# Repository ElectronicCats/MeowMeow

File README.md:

# Meow Meow
<p align="center">

<p align=center>

</p>

  Meow Meow es una tarjeta electrónica diseñada por Electronic Cats que simula algunas teclas configurables del teclado y mouse. Meow Meow tiene la característica de poder conectar cualquier material que conduzca la electricidad convirtiendo estos objetos en paneles táctiles. 
  
  Es un kit de experimentos para principiantes y expertos que buscan interactuar entre el mundo real y la tecnología. Meow Meow puede cubrir las áreas de artes plásticas, artes visuales, música, deporte, ingeniería e incluso rehabilitación física.

## ¿A quién va dirigido Meow Meow? 

Para personas de todas las edades, desde niños de 6 años hasta adultos, educadores, artistas, ingenieros, diseñadores, inventores y creadores.

## ¿Cómo funciona? 

  Meow Meow utiliza conmutación de alta capacitancia para detectar cuándo ha realizado una conexión incluso con materiales que no son muy conductores (como hojas, pasta o personas). Meow Meow también puede actuar como un teclado o un mouse. Hay diez  entradas en la placa, a las que puedes conectar los cables caimán y hacer tus propios objetos táctiles.

   La computadora ve a Meow Meow como un teclado (o mouse) común y corriente. Por lo tanto, funciona con todos los programas, sistemas operativos y páginas web, ya que todos los programas y páginas web reciben información del teclado y el mouse.

## ¿Qué materiales funcionan con Meow Meow? 

  Cualquier material que pueda conducir un poco de electricidad funcionará. Aquí hay algunos materiales que las personas han usado en nuestros talleres: Ketchup o salsa de tomate, Grafito a lápiz, Finger Paint, Limones, etc.

  Otros materiales que funcionan muy bien: plantas, monedas, cubiertos, todo lo que está mojado, la mayoría de los alimentos, papel de aluminio, agua y cientos de cosas que no hemos probado.

## ¿Qué puedo hacer?

  ¡Eso depende de ti! Digamos que cargas un programa de un piano. Luego, en lugar de usar los botones del teclado de la computadora para tocar el piano, puede conectar Meow Meow a algo divertido, como bananas, y las bananas se convierten en las teclas del piano. 

  O digamos que busca un juego Pac-Man en línea y dibujas un joystick con un lápiz. Entonces puedes jugar a Pac-Man tocando el dibujo. 

  El kit incluye todo lo que necesita: Meow Meow, cables caimán y cable USB. 

## ¿Cómo contribuir? 

¡Las contribuciones son bienvenidas! 

Por favor lee el documento [**Manual de contribución-EN**](https://github.com/ElectronicCats/electroniccats-cla/blob/main/electroniccats-contribution-manual.md) para conocer como contribuir tus cambios al proyecto.

✨ ¡Gracias a todos nuestros [contribuyentes](https://github.com/ElectronicCats/MeowMeow/graphs/contributors)! ✨

Visita [**_Electronic Cats CLA_**](https://github.com/ElectronicCats/electroniccats-cla/blob/main/electroniccats-cla.md) para más información.

Visita [**código de conducta de comunidad**](https://github.com/ElectronicCats/electroniccats-cla/blob/main/electroniccats-community-code-of-conduct.md) para leer más de la visión y que es lo que esperamos de nuestra comunidad.
## Licence

**[OSHW] MX0003 | Certified open source hardware |** [oshwa.org/cert.](https://www.oshwa.org/cert)

Firmware released under an GNU AGPL v3.0 license. See the LICENSE file for more information.

Hardware released under an CERN Open Hardware Licence v1.2. See the LICENSE_HARDWARE file for more information.

Electronic Cats is a registered trademark, please do not use if you sell these PCBs.

Electronic Cats invests time and resources providing this open source design, please support Electronic Cats and open-source hardware by purchasing products from Electronic Cats!

Designed by Electronic Cats.

17 April 2018

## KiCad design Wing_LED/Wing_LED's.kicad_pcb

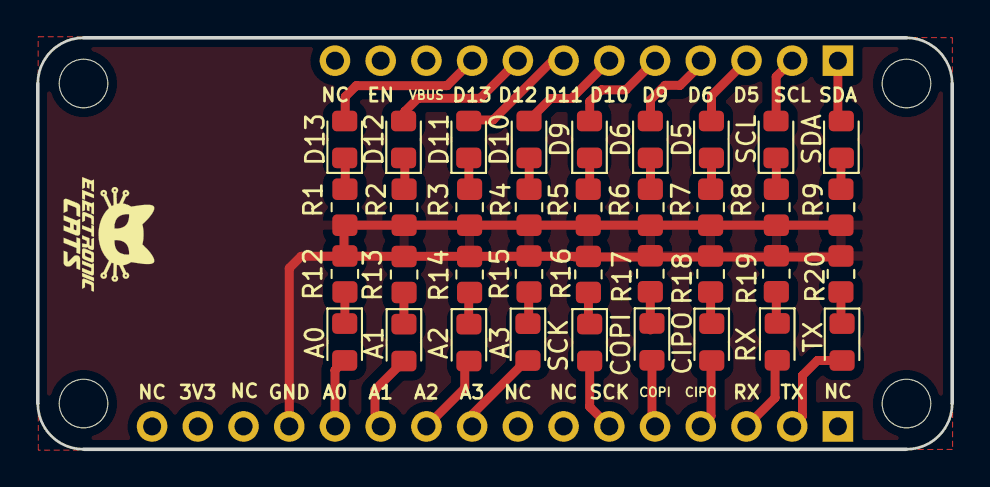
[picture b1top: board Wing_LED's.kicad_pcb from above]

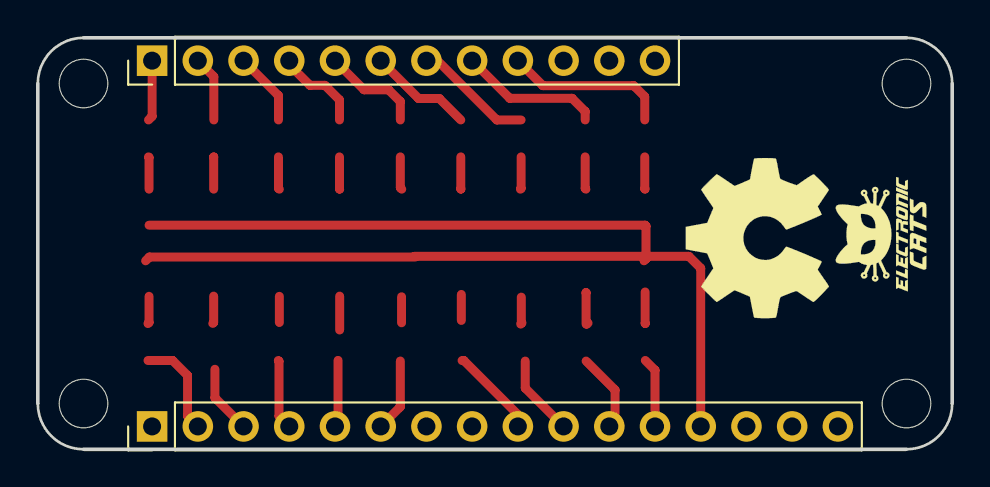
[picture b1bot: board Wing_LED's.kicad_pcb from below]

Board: 2 copper layers, 50.8 x 22.9 mm, 38 parts (2 on the bottom side), 37 nets.

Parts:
A0: A0; LED_0805_2012Metric_Pad1.15x1.40mm_HandSolder
A1: A1; LED_0805_2012Metric_Pad1.15x1.40mm_HandSolder
A2: A2; LED_0805_2012Metric_Pad1.15x1.40mm_HandSolder
A3: A3; LED_0805_2012Metric_Pad1.15x1.40mm_HandSolder
CIPO: SCK; LED_0805_2012Metric_Pad1.15x1.40mm_HandSolder
COPI: A5; LED_0805_2012Metric_Pad1.15x1.40mm_HandSolder
D5: D5; LED_0805_2012Metric_Pad1.15x1.40mm_HandSolder
D6: D6; LED_0805_2012Metric_Pad1.15x1.40mm_HandSolder
D9: D9; LED_0805_2012Metric_Pad1.15x1.40mm_HandSolder
D10: D10; LED_0805_2012Metric_Pad1.15x1.40mm_HandSolder
D11: D11; LED_0805_2012Metric_Pad1.15x1.40mm_HandSolder
D12: D12; LED_0805_2012Metric_Pad1.15x1.40mm_HandSolder
D13: D13; LED_0805_2012Metric_Pad1.15x1.40mm_HandSolder
J1: feather long; PinHeader_1x16_P2.54mm_Vertical
J2: feather short; PinHeader_1x12_P2.54mm_Vertical
R1, R2, R3, R4, R5, R6, R7, R8, R9, R12, R13, R14, R15, R16, R17, R18, R19, R20: 1K; R_0805_2012Metric_Pad1.20x1.40mm_HandSolder
RX: MOSI; LED_0805_2012Metric_Pad1.15x1.40mm_HandSolder
SCK: A4; LED_0805_2012Metric_Pad1.15x1.40mm_HandSolder
SCL: SCL; LED_0805_2012Metric_Pad1.15x1.40mm_HandSolder
SDA: SDA; LED_0805_2012Metric_Pad1.15x1.40mm_HandSolder
TX: MISO; LED_0805_2012Metric_Pad1.15x1.40mm_HandSolder

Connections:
/A0: A0.2, J1.12
/A1: A1.2, J1.11
/A2: A2.2, J1.10
/A3: A3.2, J1.9
/D5: D5.2, J2.3
/D6: D6.2, J2.4
/D9: D9.2, J2.5
/D10: D10.2, J2.6
/D11: D11.2, J2.7
/D12: D12.2, J2.8
/D13: D13.2, J2.9
/MISO: CIPO.2, J1.4
/MOSI: COPI.2, J1.5
/RX: J1.3, RX.2
/SCK: J1.6, SCK.2
/SCL: J2.2, SCL.2
/SDA: J2.1, SDA.2
/TX: J1.2, TX.2
GND: J1.13, R1.2, R2.2, R3.2, R4.2, R5.2, R6.2, R7.2, R8.2, R9.2, R12.2, R13.2, R14.2, R15.2, R16.2, R17.2, R18.2, R19.2, R20.2
unnamed: R8.1, SCL.1
unnamed: D5.1, R7.1
unnamed: D9.1, R5.1
unnamed: D6.1, R6.1
unnamed: D13.1, R1.1
unnamed: D12.1, R2.1
unnamed: D11.1, R3.1
unnamed: D10.1, R4.1
unnamed: R9.1, SDA.1
unnamed: R19.1, RX.1
unnamed: CIPO.1, R18.1
unnamed: R16.1, SCK.1
unnamed: COPI.1, R17.1
unnamed: A0.1, R12.1
unnamed: A1.1, R13.1
unnamed: A2.1, R14.1
unnamed: A3.1, R15.1
unnamed: R20.1, TX.1

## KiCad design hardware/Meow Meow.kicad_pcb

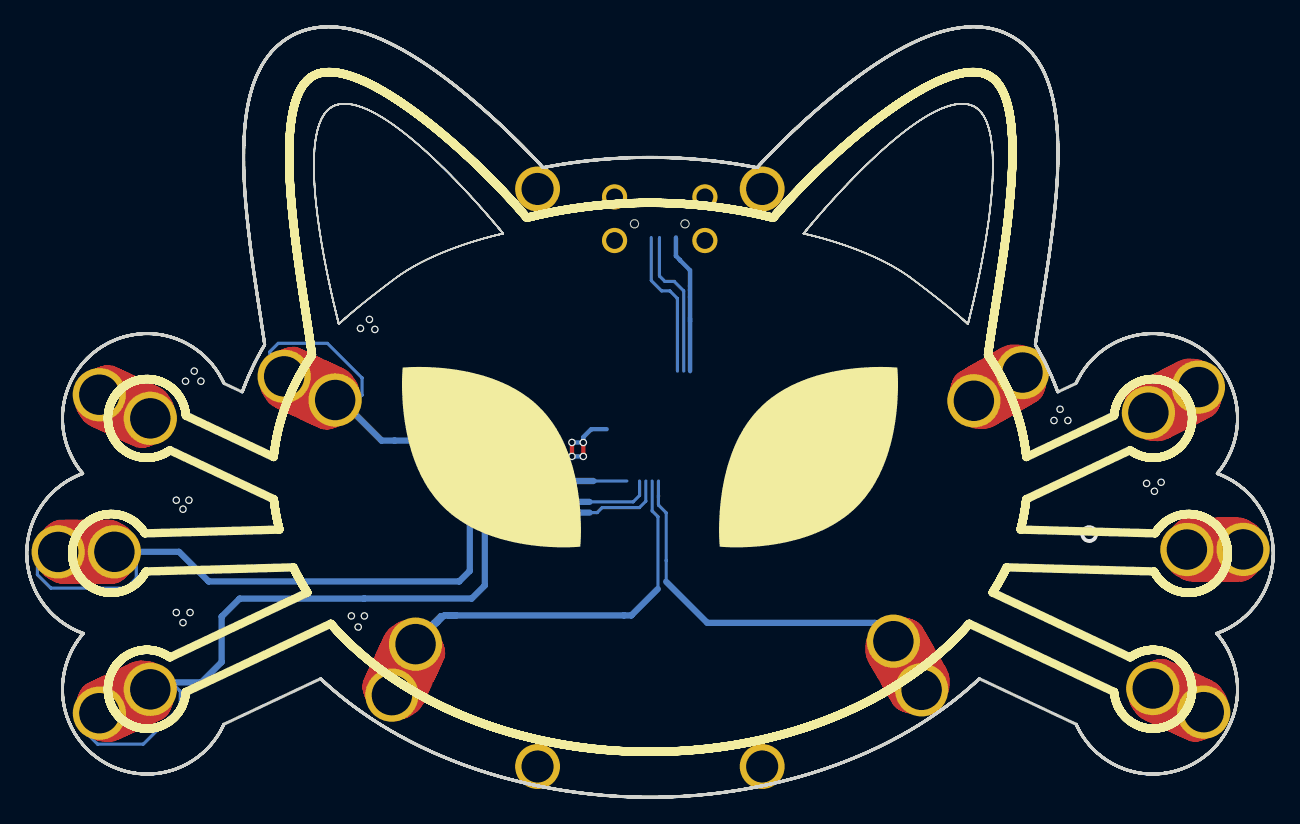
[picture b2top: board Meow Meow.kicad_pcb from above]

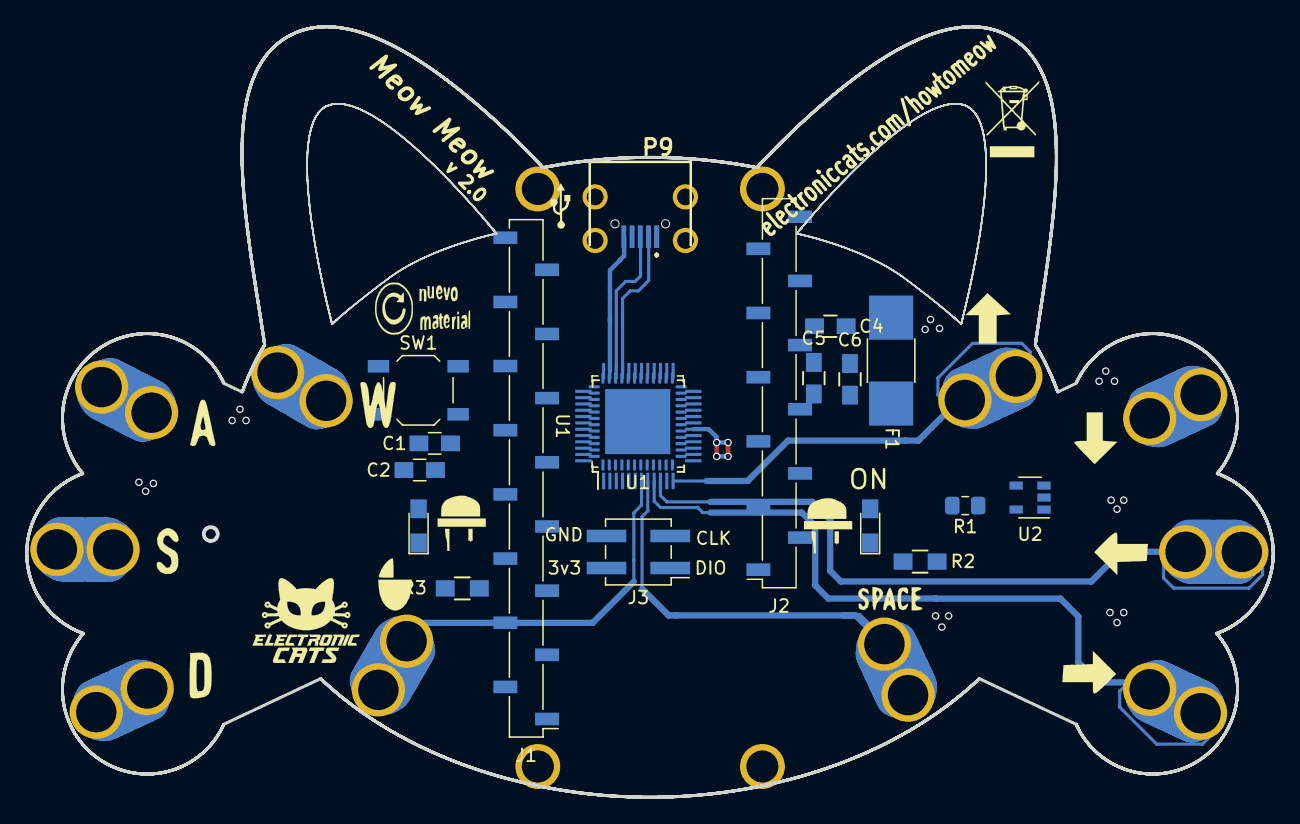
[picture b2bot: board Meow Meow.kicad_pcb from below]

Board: 2 copper layers, 98.7 x 61.0 mm, 33 parts (21 on the bottom side), 46 nets.

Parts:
C1: 1uF; C_0805_HandSoldering
C2, C5: 0.1uF; C_0805_HandSoldering
C4, C6: 10uF; C_0805_HandSoldering
D1: POWER; LED_0805_HandSoldering
D2: LED; LED_0805_HandSoldering
F1: 0.5A; R_1812_HandSoldering
J1: Conn_Left; PinSocket_1x16_P2.54mm_Vertical_SMD_Pin1Left
J2: Conn_Right; PinSocket_1x12_P2.54mm_Vertical_SMD_Pin1Right
J3: SWD; Pin_Header_Straight_2x02_Pitch2.54mm_SMD
P1: SPACE; SEWALLI_renew
P2: KEY_DOWN_ARROW; SEWALLI_renew
P3: KEY_RIGHT_ARROW; SEWALLI_renew
P5: KEY_LEFT_ARROW; SEWALLI_renew
P6: D; SEWALLI_renew
P7: S; SEWALLI_renew
P8: MOUSE_LEFT; SEWALLI_renew
P9: USB_Micro; U254051N4BH806
P10: A; SEWALLI_renew
P11: W; SEWALLI_renew
P12: KEY_UP_ARROW; SEWALLI_renew
PCB**: VAL**; PCB_FeatherWing
R1: 10K; R_0805_2012Metric_Pad1.15x1.40mm_HandSolder
R2, R3: 1K; R_0805_HandSoldering
SW1: RESET; SW_SPST_TL3342
U1: ATSAMD21G18A-M; QFN-48-1EP_7x7mm_P0.5mm_EP5.15x5.15mm
U1#2: ATSAMD21G18A-AU; TQFP-48_7x7mm_Pitch0.5mm
U2: AP2112K-3.3; SOT-23-5
svg2mod: meowmeow; svg2mod
svg2mod#2, svg2mod#3: G***; svg2mod

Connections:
+3V3: C5.1, C6.1, D1.2, J1.2, J3.2, U1#2.6, U1#2.17, U1#2.36, U1#2.44, U2.5
/A0: J1.5, U1.13
/A1: J1.6, U1.14
/A2: J1.7, U1.15
/A3: J1.8, U1.16
/D+: P9.3, U1.34, U1#2.34
/D-: P9.2, U1.33, U1#2.33
/EN: J2.2, R1.2, U2.3
/GPIO05: J2.10, U1.23, U1#2.22
/GPIO06: J2.9, U1.24, U1#2.26
/GPIO08: D2.2, U1.19, U1#2.38
/GPIO09: J2.8, U1.25, U1#2.27
/GPIO10: J2.7, U1.26, U1#2.28
/GPIO11: J2.6, U1.29, U1#2.29
/GPIO12: J2.5, U1.30, U1#2.30
/GPIO13: J2.4, U1.20, U1#2.20
/MISO: J1.13, U1.31, U1#2.21
/MOSI: J1.12, U1.27, U1#2.23
/RESET: J1.1, SW1.2, U1.40, U1#2.40
/RX: J1.14, U1.22
/SCK: J1.11, U1.28, U1#2.24
/SCL: J2.11, U1.2, U1#2.2
/SDA: J2.12, U1.1, U1#2.1
/SWCLK: J3.3, U1.45, U1#2.45
/SWDIO: J3.1, U1.46, U1#2.46
/TX: J1.15, U1.21
/Y0: P7.1, U1.3, U1#2.3
/Y1: P6.1, U1.4, U1#2.4
/Y2: P5.1, U1.9, U1#2.9
/Y3: P3.1, U1.10, U1#2.10
/Y4: P2.1, U1.11, U1#2.11
/Y5: P12.1, U1.12, U1#2.12
/Y8: P11.1, U1.47, U1#2.47
/Y9: P10.1, U1.48, U1#2.48
/Y14: P8.1, U1.7, U1#2.7
/Y15: P1.1, U1.8, U1#2.8
GND: C1.2, C2.2, C4.2, C5.2, C6.2, J1.4, J3.4, P9.5, R2.2, R3.2, SW1.1, U1.5, U1.18, U1.35, U1.42, U1#2.5, U1#2.18, U1#2.35, U1#2.42, U2.2
unnamed: C1.1, U1.43, U1#2.43
unnamed: C2.1, U1.6, U1.17, U1.36, U1.44
unnamed: D1.1, R2.1
unnamed: D2.1, R3.1
unnamed: F1.2, P9.1
unnamed: U1.37, U1#2.37
unnamed: U1.39, U1#2.39
unnamed: U1.41, U1#2.41
VBUS: C4.1, F1.1, J2.3, R1.1, U2.1

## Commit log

2018-04-20 Schematic 0.1 alpha
2018-04-27 Remove button reset
2018-04-27 Init PCB
2018-04-27 Add library for schematic
2018-04-28 Update sch library
2018-04-28 change uC
2018-04-28 Add footprint library
2018-04-30 Fix conections
2018-05-01 PCB V1
2018-05-01 check pcb
2018-05-16 Version SAMD21
2018-05-16 Add I2C, I2S, Serial and SPI port
2018-05-16 Fix label name pins X
2018-05-17 Init commit of Firmware
2018-05-17 Added DEBUG variables
2018-05-17 Fix logic activation button
2018-05-17 Keyboard work beta
2018-05-17 Keyboard working beta
2018-05-17 Define key
2018-05-17 recognition to SparkFun and Makey Makey
2018-05-17 Clean code
2018-05-17 Added mouse
2018-05-17 Debug for pressThreshold and releaseThreshold
2018-05-17 Rename object touch
2018-05-18 Added movement Events Mouse
2018-05-18 Move init tocuh to initializeInputs
2018-05-18 Rename pin with firmware beta and extra pins
2018-05-18 Schematic_v0.2
2018-05-20 Add LICENSE_HARDWARE
    CERN Open Hardware Licence v1.2
2018-05-20 Add Licence firmware
2018-05-21 OSHW
2018-05-21 Update README OSHW
2018-05-22 Added Initial Calibration
2018-05-22 Fix link certification
2018-05-24 Update lib with samd21
2018-05-24 Update netlist samd21
2018-05-24 Update componets
2018-05-24 Update cache-lib
2018-05-25 Change calibration metod
2018-05-25 Update capacitor Vddcore and leds
2018-05-30 Update BOM
2018-05-31 Update README in spanish
2018-06-07 Add figure
2018-06-07 Change Headers Expansion and SWD
2018-06-07 Update PCB
2018-06-09 PCB update
2018-06-11 added new connector
2018-06-11 Add logos
2018-06-11 place components to route
2018-06-11 Start routing
2018-06-11 Change eyes to Silks
2018-06-12 Route advaced
2018-06-12 All traces complete
2018-06-12 idk what changes are here
2018-06-12 Add logo proyectil
2018-06-19 Add pin 5v
2018-06-19 Addes bootloader uf2 default
2018-06-19 Firmware default v0.5 beta
    Firmware for restore device
2018-06-20 Fix firmware
2018-06-20 New logo
2018-06-20 Add new logo to README
2018-06-23 Name pins SWD
2018-06-28 Update default bootloader with new PID and VID USB and uf2
2018-07-25 connector 6 pin
    se quito 3V
2018-07-25 SENSOR CAPACITIVE
2018-07-25 ALINEACION
2018-07-25 Footprit new connectors
2018-07-27 Footprint connector 2x2
2018-08-16 Routeo new connectors
2018-08-16 Reacomodo de vias
2018-08-17 Plano GND back
2018-08-17 Labels
2018-08-17 Lable I2S
2018-08-20 Pre-version 1.0
2018-08-20 Change Link how to meow
2018-08-21 3D USB
2018-08-21 Fix Typo in text
2018-08-22 3D botton
2018-08-22 Update tracks
2018-09-10 Botton reset
2018-09-18 components meowmeow.lib kicad5
2018-09-18 v1.1 beta
2018-09-24 Modificacion Drill de conector USB
2018-09-24 GND PLANE
2018-09-24 Add keys logo
2018-09-25 New logos keys
2018-12-25 update bootloader arduino ide
2019-01-02 change connectors schematic
2019-01-02 Fix back pinout
2019-03-30 remove unnecessary
2019-03-30 update files
2019-03-30 add DEBUG Mouse
2019-03-30 refactor new measure update
2019-03-30 bump firmware v0.6
2019-04-01 Debug compatible with serial plotter
2019-04-01 revert value resistor
2019-04-01 bump firmware 0.6-beta2
2019-04-01 best comments error in QT sensors
2019-04-02 add recursos design
2019-04-02 change reset button
2019-04-02 update gitignore
2019-05-15 change arrows
2019-06-03 bump firmware 0.6
2019-06-03 remove version beta of 0.6
2020-02-15 update schematic headers feather
2020-02-15 update footprints
2020-02-15 cache lib
2020-02-15 clean pcb
2020-02-15 init pcb mini
2020-02-15 init sketch
2020-02-16 11 inputs capacitives! :O
2020-02-16 Update to samd11!
2020-02-16 Update pcb to SAMD11
2020-02-19 update names keys
2020-02-19 Update size
2020-02-26 Update main code for mouse moving
2020-03-03 add library and layout
2020-03-03 update logos
2020-03-03 port shezhen2svg
2020-03-03 remove firmware unsupported
2020-03-20 Update 10 inputs
2020-03-20 firmware beta
2020-03-25 Update 10 inputs and umbral value
    Update ino and bin 10 inputs values with these changes Mini Meow Meow has a correct touch
2020-03-27 Update turn on a led touching peripherals
2020-04-10 fix link error
2020-07-23 swd port change
2020-07-23 correct swd port change
2020-08-24 add binary for Manual Meow Meow
2021-06-21 update pinout and simbol
2021-06-21 change GPIO13
2021-06-22 New floorplant
2021-06-23 Finished new routing
2021-06-23 Fixed vias
2021-06-23 Fixed Labels and changed LDO
2021-06-23 modify caps
2021-06-24 update wing
2021-06-24 v2.0
2021-06-24 update project
2021-06-24 Made in Mexico with love ;)
2021-07-06 First_PCB
2021-07-08 add firmware meow meow 2
2021-07-08 Update bootloaders
2021-07-08 Update scripts uf2conv
2021-07-08 add binary firmware meow meow 2
2021-07-09 fix pins labels
2022-01-20 Update Kicad 6
2022-01-21 add firmware test wing leds
2022-01-21 add binary files wing led test
2022-01-27 Init port Arduino_MCHPTouch
2022-03-20 update schematic and footprint, mising some GPIOs check schematic
2022-03-23 new GPIOs
2022-03-30 change to SAML21G
2022-04-15 update layout
2022-04-27 update version
2022-06-13 Update_PCB
2022-06-13 Change_Labels
2022-07-04 Updated 3.1V BOM and added "HTML" and "Pos" archives
2022-07-15 Fix pins capacitive
2022-07-16 fix layou erase previous files
2022-08-09 update ino
2022-08-23 Update README.md
    Se dejo mas claro donde podia encontrar el Manual
2022-08-26 Add firmware Meow Meow 3
2022-08-26 Update description
2022-08-26 fix arrows
2022-08-26 fixed error calibration
2022-08-26 Update version3
2022-08-29 fix calibrate for Meow Meow 1
2022-08-29 fix calibrate for meow meow 2
2022-09-12 Create template for issue resol
2022-12-05 remove cap
2022-12-05 remove cap lost
2022-12-14 Add_Logo
2023-11-28 Actualizacion README
    Se agregó links a la wiki, imágenes referentes y algunas correcciones.
2023-11-28 typos
2023-12-06 Update wiki pic
    Nueva imagen para la wiki que faltaba
2023-12-26 Actualizacion readme
    Cambio boton tienda y Wiki. Se corrigio error de imagen.
2024-04-08 feat(docs);Update README.md
    Add CLA
2024-04-09 feat(docs):Update README.md
    Anadir CLA
